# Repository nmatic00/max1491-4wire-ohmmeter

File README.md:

# Low-Resistance Meter (2–200 Ω)

This is my first project.

Portable digital ohmmeter designed for accurate low-resistance measurements. This project covers the full electronic system design, including schematic, pcb, enclosure and documentation.

Developed as a coursework project for **Design of Industrial Devices and Measurement Systems 1**.
---

---

## Technical Specifications

| Parameter | Specification |
| :--- | :--- |
| **Measurement Range** | 2 Ω, 20 Ω, and 200 Ω full-scale |
| **Current Source** | 1 mA, 10 mA, and 100 mA (switch-selectable) |
| **Display** | $3\frac{1}{2}$-digit multiplexed LCD (VIM-503-DP-RC-S-HV via MAX1491) |
| **Power Supply** | Single 9 V battery (BT1) with internal +5 V regulation (LM78M05) |
| **Measurement Method** | 4-wire (Kelvin) sensing |
| **Form Factor** | 2-layer $100 \times 100\text{ mm}$ SMD PCB |

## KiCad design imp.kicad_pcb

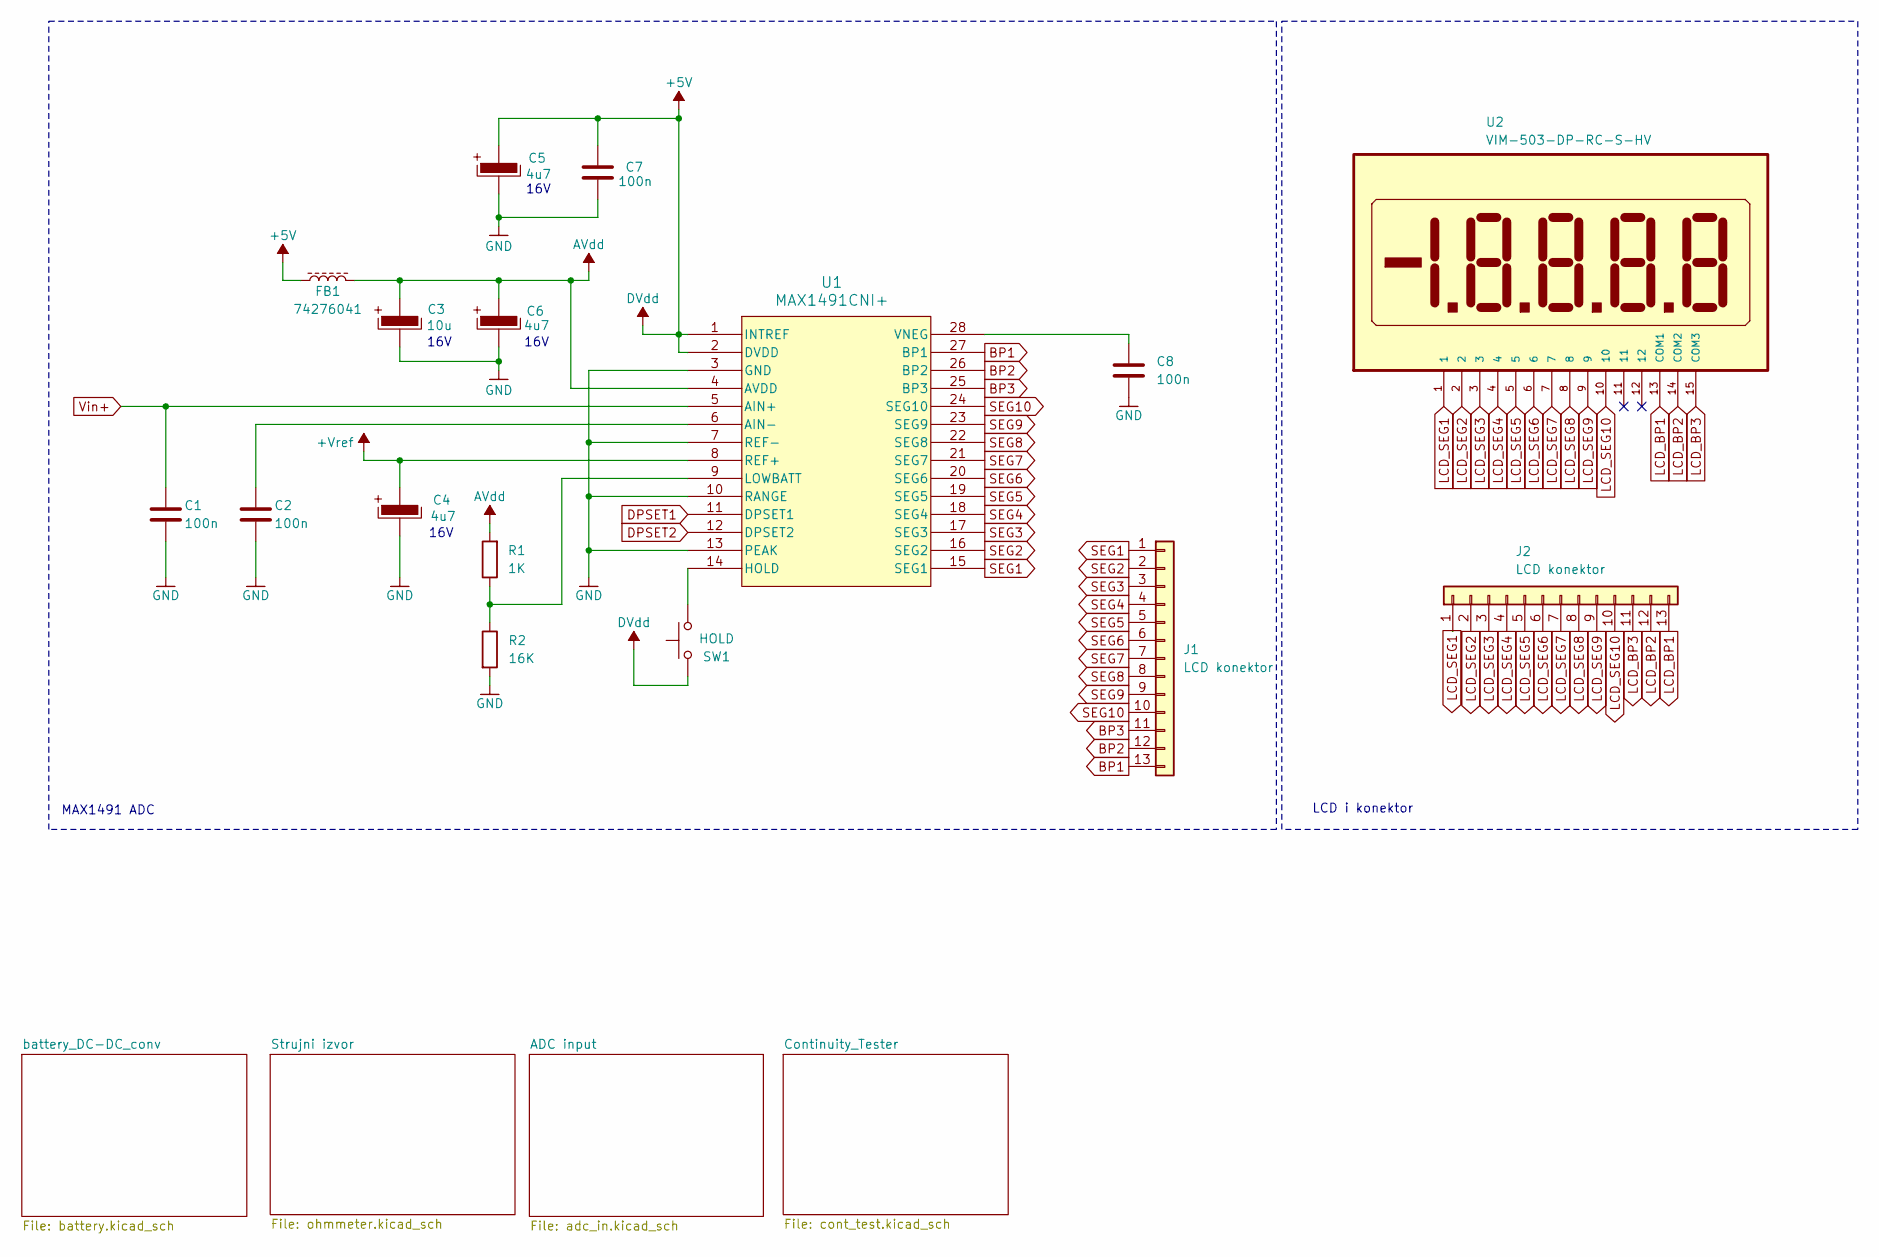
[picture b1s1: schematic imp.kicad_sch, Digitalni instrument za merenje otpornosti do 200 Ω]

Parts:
C1, C2, C7, C8: 100n; C_0603_1608Metric_Pad1.08x0.95mm_HandSolder
C3: 10u; CP_Elec_4x5.4
C4, C5, C6: 4u7; CP_Elec_4x5.4
FB1: 74276041; LairdTech_28C0236-0JW-10
J1, J2: LCD konektor; Hirose_DF13-13P-1.25DSA_1x13_P1.25mm_Vertical
R1: 1K; R_0805_2012Metric_Pad1.20x1.40mm_HandSolder
R2: 16K; R_0805_2012Metric_Pad1.20x1.40mm_HandSolder
SW1: HOLD; SW_Tactile_SPST_Angled_PTS645Vx83-2LFS
U1: MAX1491CNI+; 21-0043D_28_MXM
U2: VIM-503-DP-RC-S-HV; LCD_VIM-503-DP-RC-S-HV; DigiKey_Part_Number 153-1054-ND

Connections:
+5V: C5.1, C7.1, FB1.1, SW1.1, U1.1 (INTREF), U1.2 (DVDD); also elsewhere on the board
+Vref: C4.1, U1.8 (REF+); also elsewhere on the board
AVdd: C3.1, C6.1, FB1.2, R1.2, U1.4 (AVDD)
BP1: J1.13, U1.27 (BP1)
BP2: J1.12, U1.26 (BP2)
BP3: J1.11, U1.25 (BP3)
DPSET1: U1.11 (DPSET1); also elsewhere on the board
DPSET2: U1.12 (DPSET2); also elsewhere on the board
GND: C1.2, C2.2, C3.2, C4.2, C5.2, C6.2, C7.2, C8.2, R2.2, U1.3 (GND), U1.7 (REF-), U1.10 (RANGE), U1.13 (PEAK); also elsewhere on the board
LCD_BP1: J2.13, U2.13 (COM1)
LCD_BP2: J2.12, U2.14 (COM2)
LCD_BP3: J2.11, U2.15 (COM3)
LCD_SEG1: J2.1, U2.1
LCD_SEG2: J2.2, U2.2
LCD_SEG3: J2.3, U2.3
LCD_SEG4: J2.4, U2.4
LCD_SEG5: J2.5, U2.5
LCD_SEG6: J2.6, U2.6
LCD_SEG7: J2.7, U2.7
LCD_SEG8: J2.8, U2.8
LCD_SEG9: J2.9, U2.9
LCD_SEG10: J2.10, U2.10
unnamed: C2.1, U1.6 (AIN-)
unnamed: SW1.2, U1.14 (HOLD)
unnamed: R1.1, R2.1, U1.9 (LOWBATT)
unnamed: C8.1, U1.28 (VNEG)
SEG1: J1.1, U1.15 (SEG1)
SEG2: J1.2, U1.16 (SEG2)
SEG3: J1.3, U1.17 (SEG3)
SEG4: J1.4, U1.18 (SEG4)
SEG5: J1.5, U1.19 (SEG5)
SEG6: J1.6, U1.20 (SEG6)
SEG7: J1.7, U1.21 (SEG7)
SEG8: J1.8, U1.22 (SEG8)
SEG9: J1.9, U1.23 (SEG9)
SEG10: J1.10, U1.24 (SEG10)
Vin+: C1.1, U1.5 (AIN+); also elsewhere on the board

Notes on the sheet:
LCD i konektor
16V
MAX1491 ADC

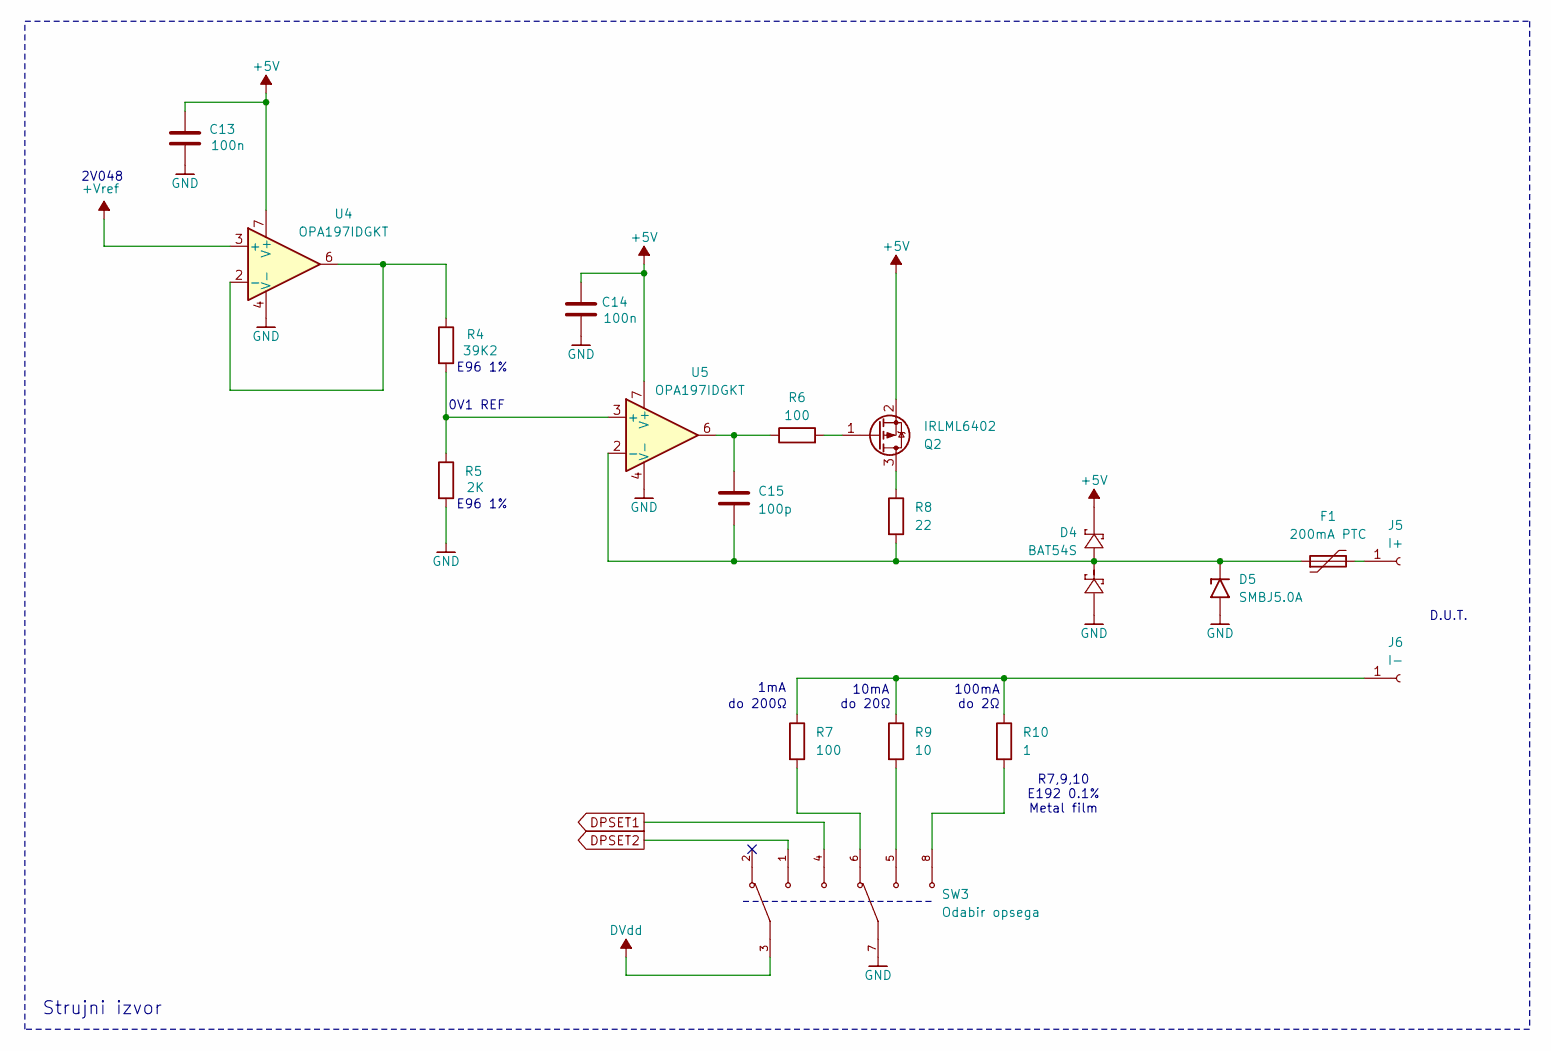
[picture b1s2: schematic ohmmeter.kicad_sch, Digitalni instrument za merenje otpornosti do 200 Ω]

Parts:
C13, C14: 100n; C_0603_1608Metric_Pad1.08x0.95mm_HandSolder
C15: 100p; C_0603_1608Metric_Pad1.08x0.95mm_HandSolder
D4: BAT54S; SOT-23
D5: SMBJ5.0A; DIOM4336X265N; PARTREV F2102
F1: 200mA PTC; Fuse_BelFuse_0ZRE0075FF_L11.5mm_W4.8mm
J5: I+; Banana_Cliff_FCR7350R_S16N-PC_Horizontal
J6: I-; Banana_Cliff_FCR7350B_S16N-PC_Horizontal
Q2: IRLML6402; SOT-23
R4: 39K2; R_0805_2012Metric_Pad1.20x1.40mm_HandSolder
R5: 2K; R_0805_2012Metric_Pad1.20x1.40mm_HandSolder
R6: 100; R_0805_2012Metric_Pad1.20x1.40mm_HandSolder
R7: 100; R_Axial_DIN0207_L6.3mm_D2.5mm_P7.62mm_Horizontal; Part No. PTF56100R00BYEB
R8: 22; R_0805_2012Metric_Pad1.20x1.40mm_HandSolder
R9: 10; R_Axial_DIN0414_L11.9mm_D4.5mm_P15.24mm_Horizontal; Part No. UPF50B10RV
R10: 1; R_Axial_DIN0309_L9.0mm_D3.2mm_P12.70mm_Horizontal; Part No. RS1/21R000BB12
SW3: Odabir opsega; SW_MHS233RA04; PARTREV C
U4, U5: OPA197IDGKT; SOIC-8_3.9x4.9mm_P1.27mm

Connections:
+5V: C13.1, C14.1, D4.2 (K), Q2.2 (S), SW3.3, U4.7 (V+), U5.7 (V+); also elsewhere on the board
+Vref: U4.3 (+); also elsewhere on the board
DPSET1: SW3.4; also elsewhere on the board
DPSET2: SW3.1; also elsewhere on the board
GND: C13.2, C14.2, D4.1 (A), D5.A, R5.2, SW3.7, U4.4 (V-), U5.4 (V-); also elsewhere on the board
unnamed: C15.1, R6.1, U5.6
unnamed: C15.2, D4.3 (COM), D5.K, F1.1, R8.2, U5.2 (-)
unnamed: F1.2, J5.1 (Pin_1_1)
unnamed: J6.1 (Pin_1_1), R7.1, R9.1, R10.1
unnamed: Q2.3 (D), R8.1
unnamed: Q2.1 (G), R6.2
unnamed: R7.2, SW3.6
unnamed: R9.2, SW3.5
unnamed: R10.2, SW3.8
unnamed: R4.1, U4.2 (-), U4.6
unnamed: R4.2, R5.1, U5.3 (+)

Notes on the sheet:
1mA
D.U.T.
E96 1%
do 20Ω
Strujni izvor
2V048
10mA
0V1 REF
R7,9,10 E192 0.1% Metal film
do 200Ω
100mA
do 2Ω

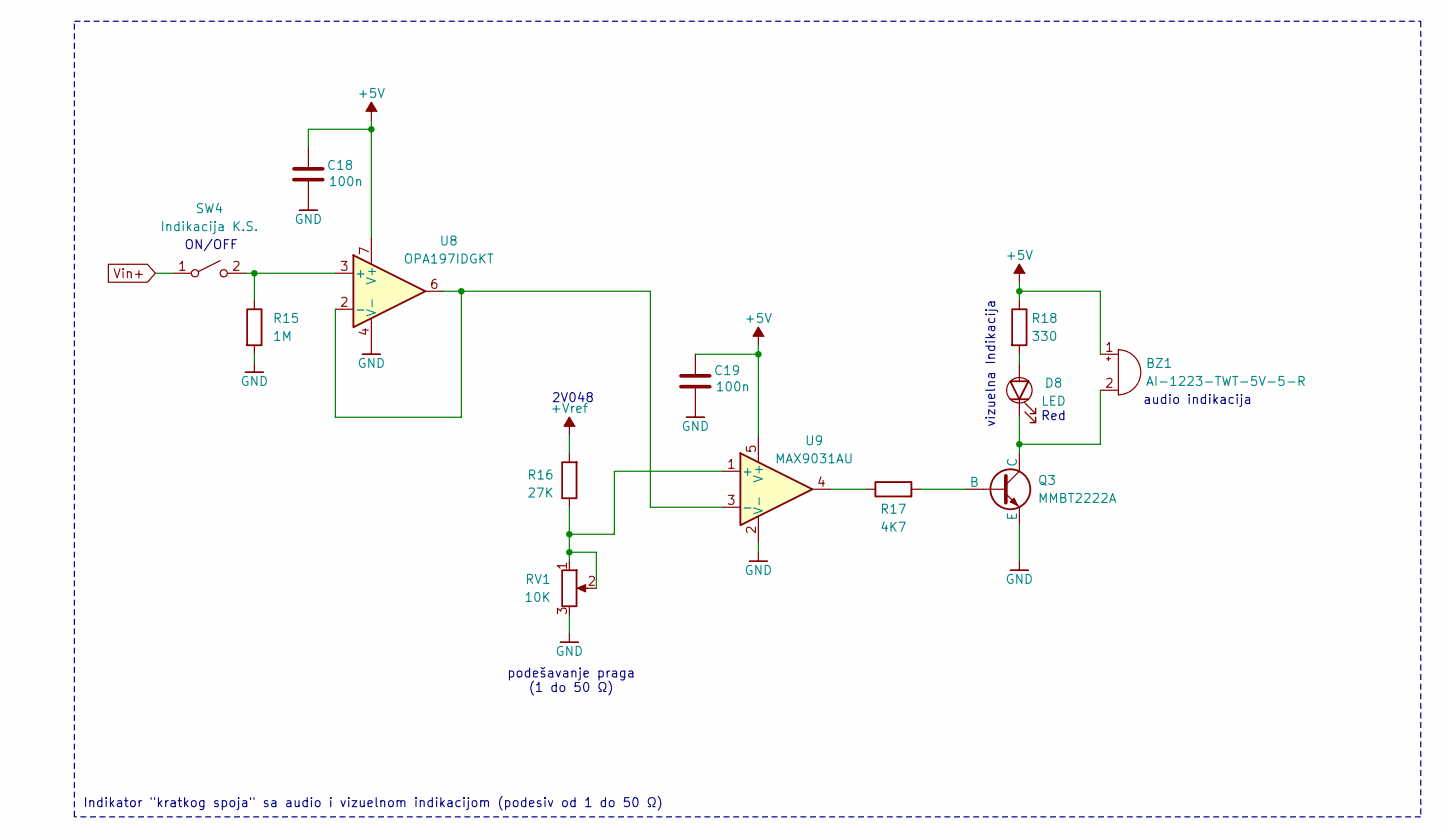
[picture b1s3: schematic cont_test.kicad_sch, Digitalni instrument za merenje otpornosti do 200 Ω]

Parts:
BZ1: AI-1223-TWT-5V-5-R; Indicator_PUI_AI-1440-TWT-24V-2-R
C18, C19: 100n; C_0603_1608Metric_Pad1.08x0.95mm_HandSolder
D8: LED; LED_D3.0mm
Q3: MMBT2222A; SOT-23
R15: 1M; R_0805_2012Metric_Pad1.20x1.40mm_HandSolder
R16: 27K; R_0805_2012Metric_Pad1.20x1.40mm_HandSolder
R17: 4K7; R_0805_2012Metric_Pad1.20x1.40mm_HandSolder
R18: 330; R_0805_2012Metric_Pad1.20x1.40mm_HandSolder
RV1: 10K; Potentiometer_Alps_RK09Y11_Single_Horizontal
SW4: Indikacija K.S.; SW_L101011ML04Q
U8: OPA197IDGKT; SOIC-8_3.9x4.9mm_P1.27mm
U9: MAX9031AU; SOT-23-5

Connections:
+5V: BZ1.1 (+), C18.1, C19.1, R18.1, U8.7 (V+), U9.5 (V+); also elsewhere on the board
+Vref: R16.2; also elsewhere on the board
GND: C18.2, C19.2, Q3.3 (E), R15.2, RV1.3, U8.4 (V-), U9.2 (V-); also elsewhere on the board
unnamed: BZ1.2 (-), D8.1 (K), Q3.1 (C)
unnamed: D8.2 (A), R18.2
unnamed: Q3.2 (B), R17.2
unnamed: R17.1, U9.4
unnamed: R15.1, SW4.2 (B), U8.3 (+)
unnamed: U8.2 (-), U8.6, U9.3 (-)
unnamed: R16.1, RV1.1, RV1.2, U9.1 (+)
Vin+: SW4.1 (A); also elsewhere on the board

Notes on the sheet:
ON/OFF
podešavanje praga (1 do 50 Ω)
Red
2V048
vizuelna Indikacija
Indikator "kratkog spoja" sa audio i vizuelnom indikacijom (podesiv od 1 do 50 Ω)
audio indikacija

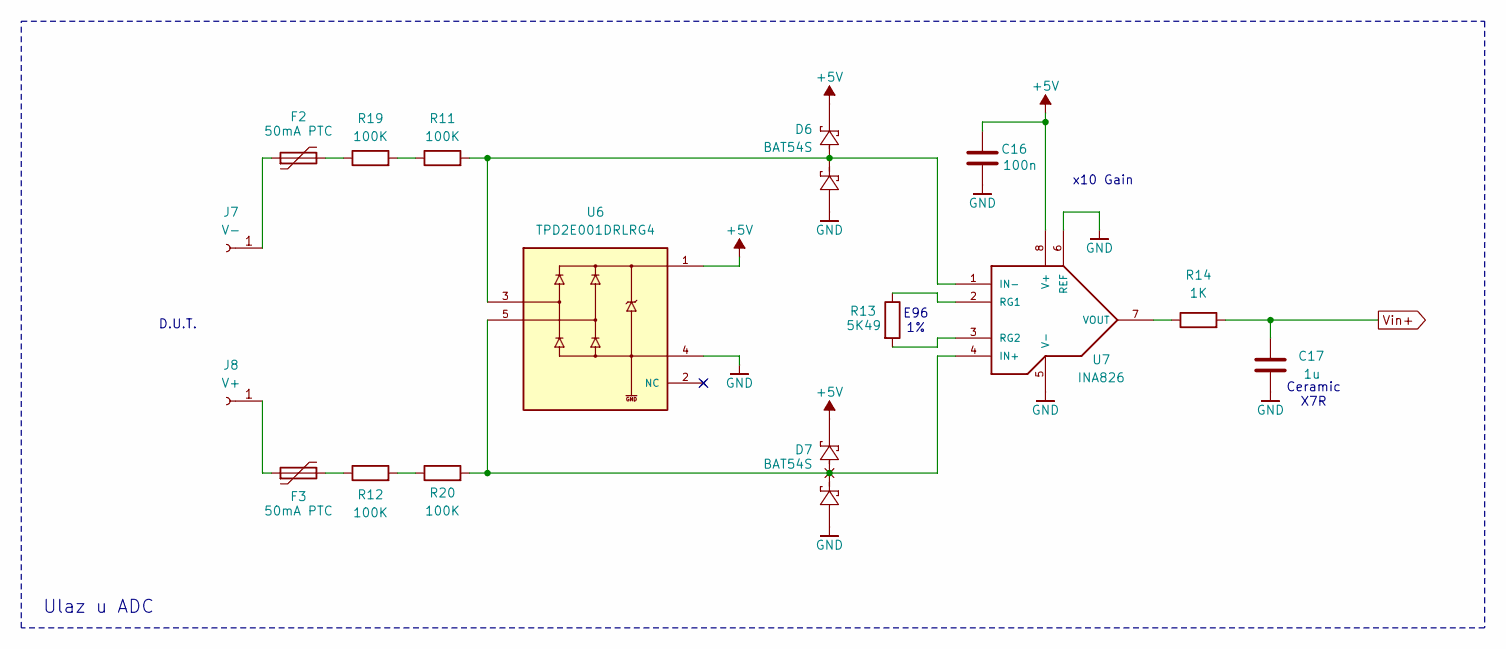
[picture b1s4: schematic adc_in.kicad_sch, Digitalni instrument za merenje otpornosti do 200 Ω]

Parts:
C16: 100n; C_0603_1608Metric_Pad1.08x0.95mm_HandSolder
C17: 1u; C_0603_1608Metric_Pad1.08x0.95mm_HandSolder
D6, D7: BAT54S; SOT-23
F2, F3: 50mA PTC; FUSE_CMF-RL50A-0_BRN
J7: V-; Banana_Cliff_FCR7350G_S16N-PC_Horizontal
J8: V+; Banana_Cliff_FCR7350G_S16N-PC_Horizontal
R11, R12, R19, R20: 100K; R_0805_2012Metric_Pad1.20x1.40mm_HandSolder
R13: 5K49; R_0805_2012Metric_Pad1.20x1.40mm_HandSolder
R14: 1K; R_0805_2012Metric_Pad1.20x1.40mm_HandSolder
U6: TPD2E001DRLRG4; SOTFL50P160X60-5N; PARTREV I
U7: INA826; SO-8

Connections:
+5V: C16.1, D6.2 (K), D7.2 (K), U6.1, U7.8 (V+); also elsewhere on the board
GND: C16.2, C17.2, D6.1 (A), D7.1 (A), U6.4, U7.5 (V-), U7.6 (REF); also elsewhere on the board
unnamed: D6.3 (COM), R11.2, U6.3, U7.1 (IN-)
unnamed: D7.3 (COM), R20.2, U6.5, U7.4 (IN+)
unnamed: F2.2, R19.1
unnamed: F3.2, R12.1
unnamed: F2.1, J7.1 (Pin_1_1)
unnamed: F3.1, J8.1 (Pin_1_1)
unnamed: R11.1, R19.2
unnamed: R12.2, R20.1
unnamed: R13.1, U7.2 (RG1)
unnamed: R13.2, U7.3 (RG2)
unnamed: R14.1, U7.7 (VOUT)
Vin+: C17.1, R14.2; also elsewhere on the board

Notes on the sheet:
x10 Gain
D.U.T.
E96 1%
Ulaz u ADC
Ceramic X7R

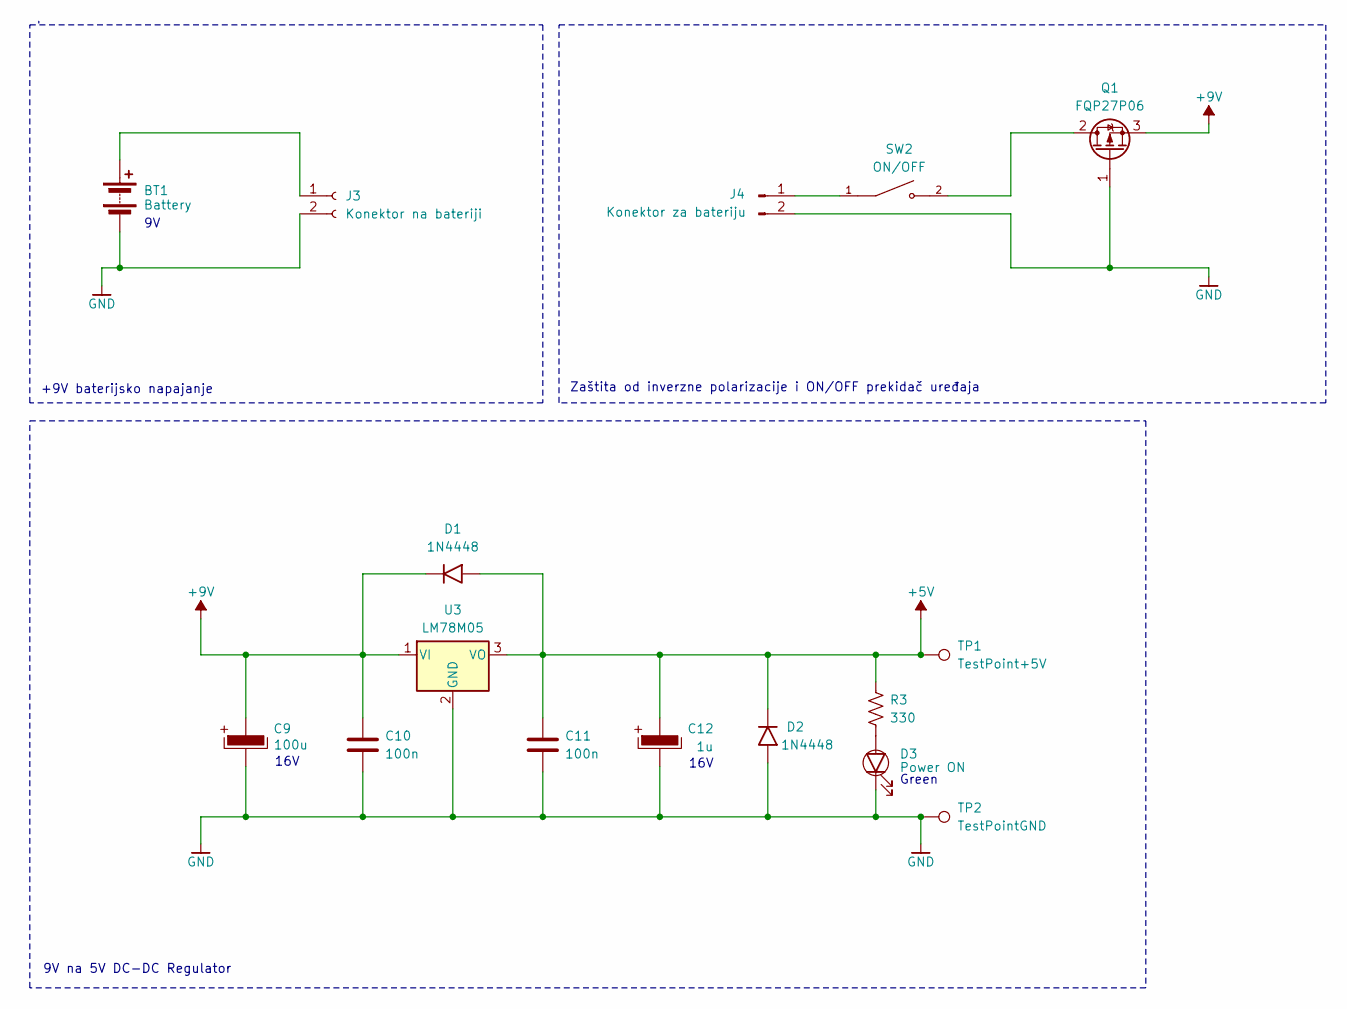
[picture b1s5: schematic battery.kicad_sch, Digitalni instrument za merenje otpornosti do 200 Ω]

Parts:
BT1: Battery; BatteryHolder_Eagle_12BH611-GR
C9: 100u; CP_Elec_6.3x5.9
C10, C11: 100n; C_0603_1608Metric_Pad1.08x0.95mm_HandSolder
C12: 1u; CP_Elec_4x4.5
D1, D2: 1N4448; D_SOD-323
D3: Power ON; LED_D3.0mm
J3: Konektor na bateriji; Molex_KK-254_AE-6410-02A_1x02_P2.54mm_Vertical
J4: Konektor za bateriju; Molex_KK-254_AE-6410-02A_1x02_P2.54mm_Vertical
Q1: FQP27P06; TO-220-3_Vertical
R3: 330; R_0805_2012Metric_Pad1.20x1.40mm_HandSolder
SW2: ON/OFF; SW_L101011ML04Q; PARTREV 19 Mar 2019
TP1: TestPoint+5V; TestPoint_Loop_D2.54mm_Drill1.5mm_Beaded
TP2: TestPointGND; TestPoint_Loop_D2.54mm_Drill1.5mm_Beaded
U3: LM78M05; TO-252-2

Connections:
+5V: C11.1, C12.1, D1.2 (A), D2.1 (K), R3.1, TP1.1 (1_1), U3.3 (VO); also elsewhere on the board
+9V: C9.1, C10.1, D1.1 (K), Q1.3 (S), U3.1 (VI)
GND: BT1.2 (-), C9.2, C10.2, C11.2, C12.2, D2.2 (A), D3.1 (K), J3.2, J4.2, Q1.1 (G), TP2.1 (1_1), U3.2 (GND); also elsewhere on the board
unnamed: BT1.1 (+), J3.1
unnamed: D3.2 (A), R3.2
unnamed: J4.1, SW2.1
unnamed: Q1.2 (D), SW2.2

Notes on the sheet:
16V
9V na 5V DC-DC Regulator
+9V baterijsko napajanje
Green
Zaštita od inverzne polarizacije i ON/OFF prekidač uređaja

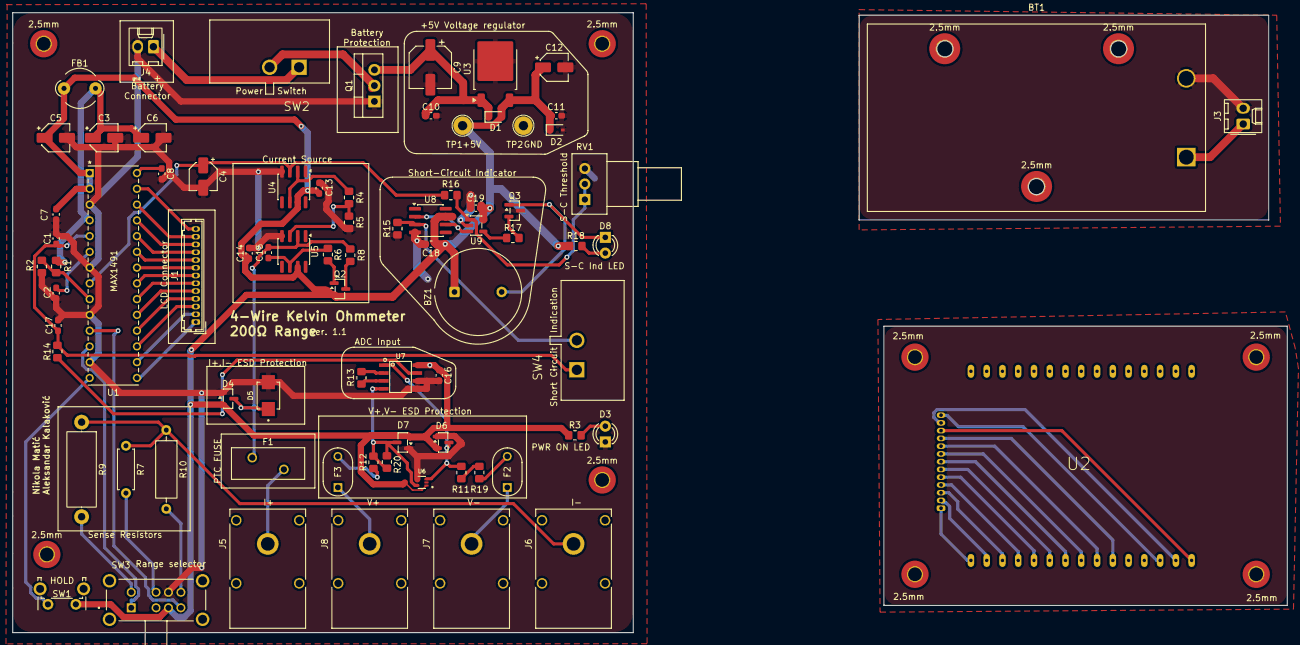
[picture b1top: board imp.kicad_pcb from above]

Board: 2 copper layers, 100.0 x 99.9 mm, 91 parts (1 on the bottom side), 71 nets.

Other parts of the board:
2.5mm, 2.5mm#2, 2.5mm#4: MountingHole_2.5mm_Pad_TopBottom
2.5mm#3, 2.5mm#5, 2.5mm#6, 2.5mm#7, 2.5mm#8, 2.5mm#9, 2.5mm#10, 2.5mm#11: MountingHole_2.2mm_M2_Pad_TopBottom
